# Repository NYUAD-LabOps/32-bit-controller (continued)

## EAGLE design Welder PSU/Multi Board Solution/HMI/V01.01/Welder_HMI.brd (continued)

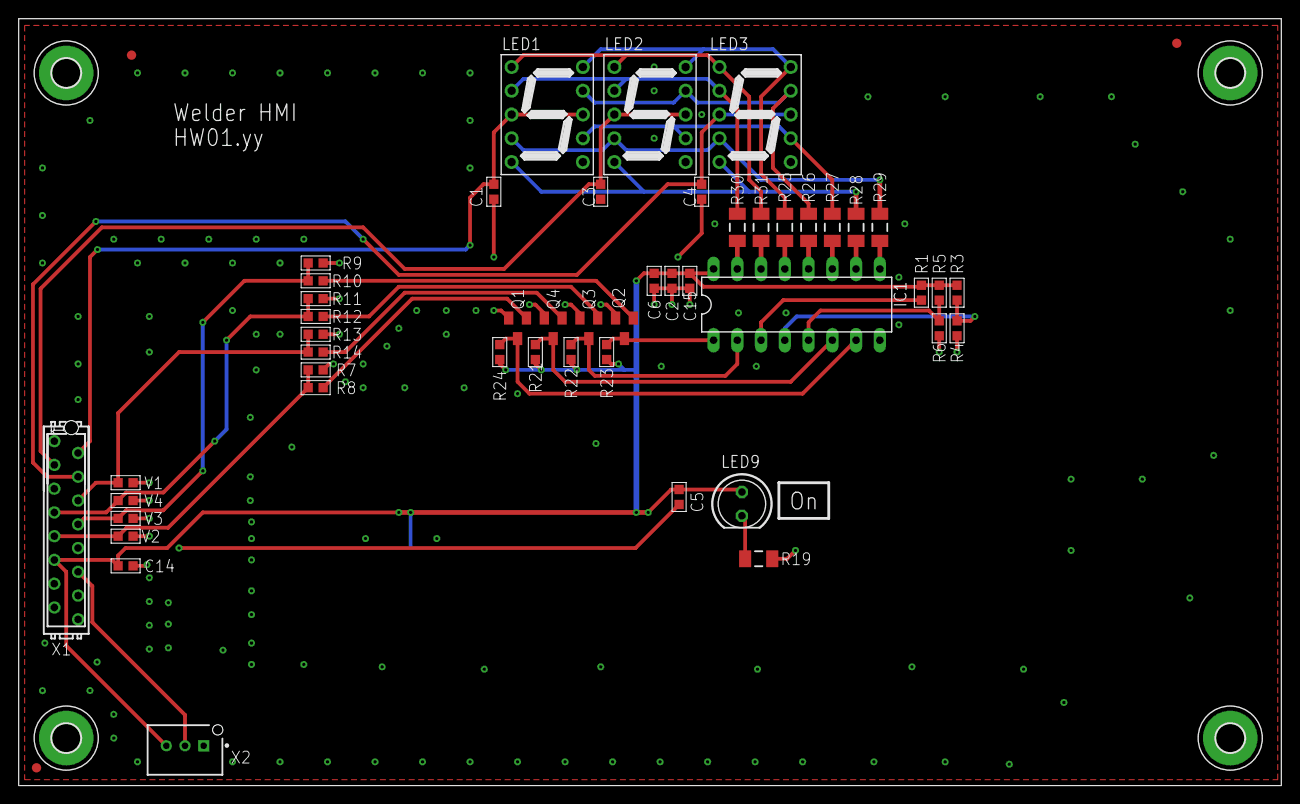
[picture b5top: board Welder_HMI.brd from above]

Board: 2 copper layers, 135.0 x 82.0 mm, 55 parts (0 on the bottom side), 36 nets.

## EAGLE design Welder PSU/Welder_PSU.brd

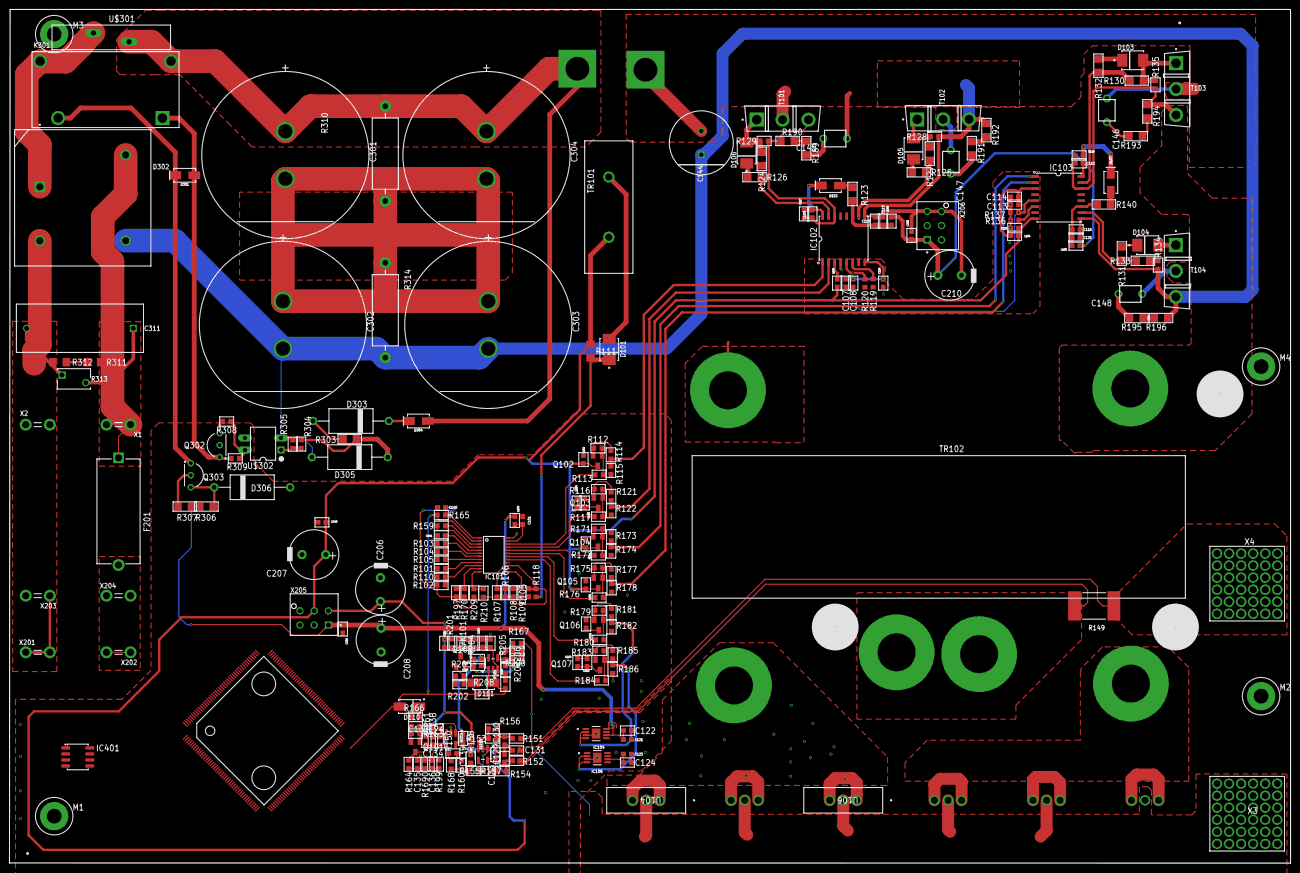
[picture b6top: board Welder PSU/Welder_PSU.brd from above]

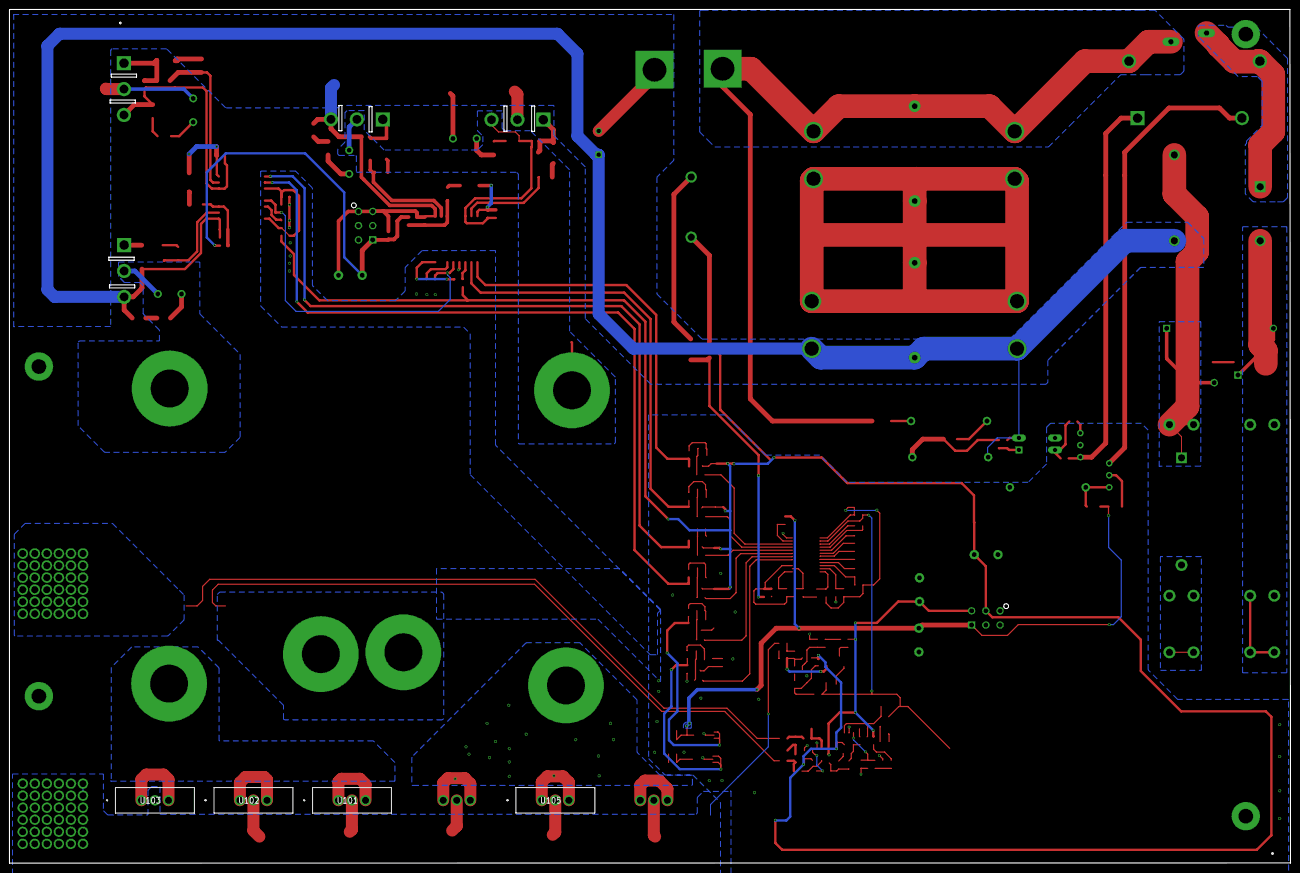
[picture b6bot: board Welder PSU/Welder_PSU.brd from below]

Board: 2 copper layers, 270.1 x 180.0 mm, 246 parts (4 on the bottom side), 126 nets.

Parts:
47K101: R0603
C101, C121, C123, C140: 1µF/25V; 0603
C102, C103, C104, C106, C111, C112: 100nF/50V; 0603
C105: 1nF 50V; C0603
C107, C113, C114, C117, C125, C141: 100nF/100V; 0603
C108, C126: 1uF/35V; 0603
C109, C110, C115, C116, C119, C120: 2.2µF/25V; 0603
C118, C122, C124, C133: 100nF/16V; 0603
C129, C130, C132, C134, C137, C138, C151, C152: 1nF 50V; 0603
C131: 100pF 50V; 0603
C135, C149: 100nF 50V; 0603
C136, C150: 220nF 50V; 0603
C139: 100nF 25V; 0603
C142, C143: 1uF/25V; 0603
C144: 860011378008; RADIAL_D13.0P5.0H25.0
C145, C146, C147, C148: FG26X7R2J472KNT06; CAP_DISC_P5H13
C153: 10nF 25V; 0603
C201, C202, C203, C205: 100nF/ 100V; 0603
C206, C207, C208, C210: 50PX470MEFC10X20; CAPACITOR-ELKO-RM5-10X16
C301, C302, C303, C304: C_1500UFCAP_SLP152M250H9P3_MODIFIED; CAP_SLP152M250H9P3_MODIFIED
C311: R49AN347050B1MKEMET_R49AN347050B1M_0_0; KEMET_R49AN347050B1M_0
D101, D103, D104, D105, D106: STTH1R04U; SMB
D102, D107, D301, D304: RS1M-13-F; SMA-DIODE
D110, D111: SS14; SMA
D302: GBPC3510W1.5MM_DRILL; GBPC3510W_MODIFIED
D303: 1N5387BRLG; DO-201AD
D305, D306: BZX79C9V1; DO-201AD
F201: 696101000002; FUSE_RM22.6
IC101: UCC28951PWR; TSSOP24
IC102, IC103: UCC21542DWK; SOIC16_HV
IC104, IC106: UCC27524DGNVSS; VSSOP-8
IC105, IC108: OPA378AIDBVR; SOT-23-5
IC401: SN65HVD3082EDR; SOIC8
K301: PANASONIC_ALFG2PF09_MODIFIED; PANASONIC_ALFG2PF09_0_MODIFIED
L102, L103, L104, L105, L108: BLM18RK601SN1D; 0603
M1, M2, M3, M4: M_HOLE_3M; PCB_SCREW_M3_POWER
PAD101, PAD102: THT_PAD_5MM; THT_PAD_D5.0
Q101, Q102, Q103, Q104, Q105, Q106, Q107, Q108: 2N7002; SOT23
Q302: KSD1616AYTA; TO-92
Q303: BC640TA; TO-92
R101, R102, R105, R199: 100K 1%; R0603
R103, R104, R107, R109, R115, R122, R158, R162, R163, R174, R178, R182, R186, R202, R203: 10K 1%; R0603
R106, R108, R159, R166, R208, R210: 0R 1%; R0603
R110: 49K9 1%; R0603
R111: 10R 1%; R1206
R112, R116, R171, R175, R179, R183: 100R 1%; R0603
R113, R117, R172, R176, R180, R184: 10R 1%; R0603
R114, R121, R173, R177, R181, R185: 330R; R0603
R118: 22R 1%; R0603
R119, R120, R136, R137: 10K; R0603
R123, R124, R125, R126, R127, R130, R131, R132, R133, R140: 2R2 1%; R1206
R128, R129, R134, R135: 49K9; R0603
R149: WSL5931L3000FEA; WSLP3921
R150, R207: 100k 1%; R0603
R151, R152: 590R 1%; R0603
R153, R154: 412R 1%; R0603
R155, R156, R1690: 47K 1%; R0603
R157, R167: 1K2 1%; R0603
R160, R200, R308, R309: R0603
R161, R201: 1k; R0603
R164, R204, R205: 100K; R0603
R165: 18K 1%; R0603
R168, R206: 18k 1%; R0603
R170, R197, R209: 10k 1%; R0603
R189, R190, R191, R192, R193, R194, R195, R196: 10K; R1206
R303: 82K, 1%; R1206
R304: 36K,5%; R0603
R305: 100K,5%; R0603
R306: 100R 1%; R1206
R307: 1K 1%; R1206
R310, R314: 51K 5%; RES-RM20-RSF3W
R311, R312: 220K 5% CRCW1206220KJNEAHP; R1206
R313: B72205S0271K1011; EPCOS_B72205S0271K101_MODIFIED
T101, T102, T103, T104: SIHG039N60EF"; TO-247AC_MODIFIED
TR101: CST206-2A1.5MM-DRILL; CST206-2A_MODIFIED
TR102: TRANSFORMER-CUSTOM-PSFB; TOROID_B64290A0705X830
U101, U102, U103, U104, U105, U106: FEP30DP-E3/45; TO-247AD_VIS
U401: S7G2LQFP176; LQFP176_24X24
U$101: OPA378AIDBVR; SOT-23-5
U$301: B57364S100M54; VARISTOR_D25_P7.5
U$302: PC817; DIP04
X1, X2, X201, X202, X203, X204: 726386-2; TE_726386-2_MODIFIED
X3: 7461061; X01_M10_7461061
X4: 7461061"; X01_M10_7461061_MODIFIED
X205, X206: MOLEX_206832-0601MOLEX_206832-0601; MOLEX_206832-0601

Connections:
10_PSFB_CONVERTER:AN_OUTA: IC102.15, R124.2, R126.2
10_PSFB_CONVERTER:AN_OUTB: IC102.10, R125.2, R127.2
10_PSFB_CONVERTER:AN_OUTC: IC103.15, R130.2, R132.2
10_PSFB_CONVERTER:AN_OUTD: IC103.10, R131.2, R133.2
10_PSFB_CONVERTER:CTRLR_OUTA: IC101.22, R113.1
10_PSFB_CONVERTER:CTRLR_OUTB: IC101.21, R117.1
10_PSFB_CONVERTER:CTRLR_OUTC: IC101.20, R172.1
10_PSFB_CONVERTER:CTRLR_OUTD: IC101.19, R176.1
10_PSFB_CONVERTER:CTRLR_OUTE: IC101.18, R180.1
10_PSFB_CONVERTER:CTRLR_OUTF: IC101.17, R184.1
10_PSFB_CONVERTER:EA_IN: D110.2, D111.2, IC101.2, R165.2, R166.1, R208.1
10_PSFB_CONVERTER:GATE_DRV_DIS: IC102.5, IC103.5, R120.1, R137.1
10_PSFB_CONVERTER:G_DRV_INA: IC102.1, R114.1, R115.1
10_PSFB_CONVERTER:G_DRV_INB: IC102.2, R121.1, R122.1
10_PSFB_CONVERTER:G_DRV_INC: IC103.1, R173.1, R174.1
10_PSFB_CONVERTER:G_DRV_IND: IC103.2, R177.1, R178.1
10_PSFB_CONVERTER:G_DRV_INE: IC104.2, IC104.4, R181.1, R182.1
10_PSFB_CONVERTER:G_DRV_INF: IC106.2, IC106.4, R185.1, R186.1
10_PSFB_CONVERTER:N$1: IC101.12, R209.2, R210.1
10_PSFB_CONVERTER:N$2: IC101.6, R103.2
10_PSFB_CONVERTER:N$3: IC101.7, R104.2
10_PSFB_CONVERTER:N$4: IC101.8, R105.2
10_PSFB_CONVERTER:N$5: IC102.6, R119.1
10_PSFB_CONVERTER:N$6: IC101.14, R106.2, R107.2
10_PSFB_CONVERTER:N$7: IC101.9, R101.1
10_PSFB_CONVERTER:N$8: IC101.13, R108.2, R109.2
10_PSFB_CONVERTER:N$9: IC101.10, R102.2, R110.2
10_PSFB_CONVERTER:N$10: D106.1, R126.1
10_PSFB_CONVERTER:N$11: D101.2, TR101.1
10_PSFB_CONVERTER:N$12: D101.1, R111.1, R118.2
10_PSFB_CONVERTER:N$13: Q102.1, R112.1, R113.2
10_PSFB_CONVERTER:N$14: Q102.2, R112.2, R114.2
10_PSFB_CONVERTER:N$15: C116.1, C120.1, IC103.11, L105.2, R140.1
10_PSFB_CONVERTER:N$16: D105.1, R125.1
10_PSFB_CONVERTER:N$17: Q103.1, R116.1, R117.2
10_PSFB_CONVERTER:N$18: Q103.2, R116.2, R121.2
10_PSFB_CONVERTER:N$19: C107.2, C108.2, C125.2, IC102.3, IC102.8, L102.2
10_PSFB_CONVERTER:N$20: C109.1, C117.2, D102.C, IC102.16
10_PSFB_CONVERTER:N$21: D105.2, R127.1, R128.2, T102.1
10_PSFB_CONVERTER:N$22: D102.A, R123.2
10_PSFB_CONVERTER:N$23: C110.1, C119.1, IC102.11, L103.1, R123.1
10_PSFB_CONVERTER:N$24: D106.2, R124.1, R129.2, T101.1
10_PSFB_CONVERTER:N$26: TR102.3, U101.1, U101.3, U102.1, U102.3, U103.1, U103.3
10_PSFB_CONVERTER:N$27: IC103.6, R136.1
10_PSFB_CONVERTER:N$28: C113.2, C114.2, C126.2, IC103.3, IC103.8, L104.1
10_PSFB_CONVERTER:N$29: TR102.6, U104.1, U104.3, U105.1, U105.3, U106.1, U106.3
10_PSFB_CONVERTER:N$30: D103.1, R132.1
10_PSFB_CONVERTER:N$31: C115.1, C118.2, D107.C, IC103.16
10_PSFB_CONVERTER:N$32: C101.1, IC101.23, L108.1
10_PSFB_CONVERTER:N$33: D104.1, R131.1
10_PSFB_CONVERTER:N$34: D104.2, R133.1, R134.2, T104.1
10_PSFB_CONVERTER:N$35: C145.2, R189.2
10_PSFB_CONVERTER:N$36: D107.A, R140.2
10_PSFB_CONVERTER:N$38: D103.2, R130.1, R135.2, T103.1
10_PSFB_CONVERTER:N$39: Q104.1, R171.1, R172.2
10_PSFB_CONVERTER:N$40: Q104.2, R171.2, R173.2
10_PSFB_CONVERTER:N$45: IC101.11, R170.2, R197.2
10_PSFB_CONVERTER:N$47: C129.1, R152.1, R154.1
10_PSFB_CONVERTER:N$48: C129.2, C130.1, C131.2
10_PSFB_CONVERTER:N$49: C130.2, R151.1, R153.1
10_PSFB_CONVERTER:N$50: R153.2, R156.2, U$101.3
10_PSFB_CONVERTER:N$51: R154.2, R155.2, U$101.4
10_PSFB_CONVERTER:N$52: R155.1, R157.2, U$101.1
10_PSFB_CONVERTER:N$53: R189.1, R190.2
10_PSFB_CONVERTER:N$54: C134.1, R160.1
10_PSFB_CONVERTER:N$55: IC101.4, R159.2
10_PSFB_CONVERTER:N$56: Q101.3, R161.1, R164.2
10_PSFB_CONVERTER:N$57: C135.1, R164.1, R1690.2
10_PSFB_CONVERTER:N$58: C136.1, IC108.3, R199.2, R1690.1
10_PSFB_CONVERTER:N$59: C137.2, R150.2
10_PSFB_CONVERTER:N$61: Q101.1, R162.1, R163.2
10_PSFB_CONVERTER:N$62: Q105.1, R175.1, R176.2
10_PSFB_CONVERTER:N$63: C137.1, C138.1, D110.1, IC108.1, R166.2
10_PSFB_CONVERTER:N$64: IC101.3, R159.1
10_PSFB_CONVERTER:N$65: Q105.2, R175.2, R177.2
10_PSFB_CONVERTER:N$66: C147.2, R191.2
10_PSFB_CONVERTER:N$67: Q106.1, R179.1, R180.2
10_PSFB_CONVERTER:N$68: Q106.2, R179.2, R181.2
10_PSFB_CONVERTER:N$69: R191.1, R192.2
10_PSFB_CONVERTER:N$70: Q107.1, R183.1, R184.2
10_PSFB_CONVERTER:N$71: Q107.2, R183.2, R185.2
10_PSFB_CONVERTER:N$72: R195.1, R196.2
10_PSFB_CONVERTER:N$73: C148.2, R195.2
10_PSFB_CONVERTER:N$74: R193.1, R194.2
10_PSFB_CONVERTER:N$75: C146.2, R193.2
10_PSFB_CONVERTER:N$76: Q108.3, R201.1, R204.2
10_PSFB_CONVERTER:N$77: C134.2, C138.2, IC108.4, R150.1, R168.2
10_PSFB_CONVERTER:N$78: 47K101.2, C149.1, R204.1
10_PSFB_CONVERTER:N$79: 47K101.1, C150.1, IC105.3, R205.2
10_PSFB_CONVERTER:N$80: Q108.1, R202.1, R203.2
10_PSFB_CONVERTER:N$81: C151.2, R207.2
10_PSFB_CONVERTER:N$82: C151.1, C152.1, D111.1, IC105.1, R208.2
10_PSFB_CONVERTER:N$83: C132.1, R200.1
10_PSFB_CONVERTER:N$84: C132.2, C152.2, IC105.4, R206.2, R207.1
10_PSFB_CONVERTER:VREF: C140.1, IC101.1, R102.1, R165.1, R197.1, R209.1
10_PSFB_CONVERTER:VSS_A: C109.2, C117.1, C147.1, IC102.14, R129.1, R190.1, T101.3, T102.2, TR102.2
10_PSFB_CONVERTER:VSS_C: C115.2, C118.1, C148.1, IC103.14, R135.1, R194.1, T103.3, T104.2, TR102.1
10_PSFB_CONVERTER:V_CS_F: C105.1, IC101.15, R106.1, R108.1, R118.1
10_PSFB_CONVERTER:V_FEEDBACK: R167.1, R200.2, R206.1
10_PSFB_CONVERTER:V_I_FEEDBACK: R157.1, R158.2, R160.2, R168.1
20_POWER_SUPPLY:N$1: F201.2, X202.1, X202.1-2, X204.1, X204.1-2
30_MAINS_INPUT_PFC1:GND_LV: D301.A, K301.1, Q303.1, R309.1
30_MAINS_INPUT_PFC1:N$1: C301.2, C302.1, C303.1, C304.2, R310.1, R314.2
30_MAINS_INPUT_PFC1:N$2: D302.1, K301.4, U$301.1
30_MAINS_INPUT_PFC1:N$3: D301.C, K301.2, Q302.1
30_MAINS_INPUT_PFC1:N$5: Q302.2, R306.2
30_MAINS_INPUT_PFC1:N$6: D303.K, D304.C
30_MAINS_INPUT_PFC1:N$7: D303.A, R303.2
30_MAINS_INPUT_PFC1:N$8: R304.2, R305.1, U$302.1
30_MAINS_INPUT_PFC1:N$9: D305.K, R303.1, R304.1
30_MAINS_INPUT_PFC1:N$12: D306.K, Q302.3, R307.2
30_MAINS_INPUT_PFC1:N$13: R311.1, R312.2
30_MAINS_INPUT_PFC1:N$16: Q303.3, R308.1
30_MAINS_INPUT_PFC1:N$17: R308.2, R309.2, U$302.4
GND: C101.2, C102.1, C103.1, C104.1, C105.2, C106.1, C107.1, C108.1, C111.1, C112.1, C113.1, C114.1, C121.2, C122.1, C123.2, C124.1, C125.1, C126.1, C131.1, C133.2, C135.2, C136.2, C139.2, C140.2, C141.2, C142.2, C143.2, C149.2, C150.2, C153.2, C201.2, C202.2, C205.2, C206.2, C207.2, C208.2, D306.A, IC101.24, IC102.4, IC103.4, IC104.3, IC104.3-2, IC105.2, IC106.3, IC106.3-2, IC108.2, M1.1, Q101.2, Q108.2, Q303.2, R101.2, R103.1, R104.1, R105.1, R107.1, R109.1, R110.1, R111.2, R115.2, R119.2, R120.2, R122.2, R136.2, R137.2, R149.1, R152.2, R156.1, R163.1, R170.1, R174.2, R178.2, R182.2, R186.2, R199.1, R203.1, R205.1, R210.2, TR101.2, TR102.4, TR102.5, U$101.2, U$302.3, X205.5, X205.6
GND2: C110.2, C116.2, C119.2, C120.2, C144.1, C203.2, C210.2, C302.2, C303.2, D302.3, D305.A, IC102.9, IC103.9, R128.1, R134.1, R192.1, R196.1, R305.2, R314.1, T102.3, T104.3, U$302.2, X206.5, X206.6
MAINS_L: C311.1, D302.4, F201.1, R311.2, R313.2, X1.1, X1.1-2
MAINS_N: C311.2, D302.2, R312.1, R313.1, X2.1, X2.1-2, X201.1, X201.1-2, X203.1, X203.1-2
unnamed: C141.1, IC101.5
unnamed: R167.2, U101.2, U102.2, U103.2, U104.2, U105.2, U106.2, X3.1, X3.1-1, X3.1-2, X3.1-3, X3.1-4, X3.1-5, X3.1-6, X3.1-7, X3.1-8, X3.1-9, X3.1-10, X3.1-11, X3.1-12, X3.1-13, X3.1-14, X3.1-15, X3.1-16, X3.1-17, X3.1-18, X3.1-19, X3.1-20, X3.1-21, X3.1-22, X3.1-23, X3.1-24, X3.1-25, X3.1-26, X3.1-27, X3.1-28, X3.1-29, X3.1-30, X3.1-31, X3.1-32, X3.1-33, X3.1-34, X3.1-35
V_3V3: C102.2, C103.2, C104.2, C106.2, C133.1, C139.1, C143.1, C153.1, C201.1, C207.1, IC105.5, IC108.5, L102.1, L104.2, Q102.3, Q103.3, Q104.3, Q105.3, U$101.5, X205.4
V_5V0: C202.1, C206.1, R158.1, R161.2, R201.2, X205.2
V_12V0: C111.2, C112.2, C121.1, C122.2, C123.1, C124.2, C142.1, C205.1, C208.1, IC104.6, IC106.6, L108.2, Q106.3, Q107.3, R306.1, R307.1, X205.1
V_12V0_AUX: C203.1, C210.1, L103.2, L105.1, X206.1
V_RECT_F_PLUS: C144.2, C145.1, C146.1, C301.1, C304.1, D304.A, K301.3, PAD101.P$1, PAD102.P$1, R310.2, T101.2, T103.2, U$301.2
WELD-: R149.2, R151.2, X4.1, X4.1-1, X4.1-2, X4.1-3, X4.1-4, X4.1-5, X4.1-6, X4.1-7, X4.1-8, X4.1-9, X4.1-10, X4.1-11, X4.1-12, X4.1-13, X4.1-14, X4.1-15, X4.1-16, X4.1-17, X4.1-18, X4.1-19, X4.1-20, X4.1-21, X4.1-22, X4.1-23, X4.1-24, X4.1-25, X4.1-26, X4.1-27, X4.1-28, X4.1-29, X4.1-30, X4.1-31, X4.1-32, X4.1-33, X4.1-34, X4.1-35

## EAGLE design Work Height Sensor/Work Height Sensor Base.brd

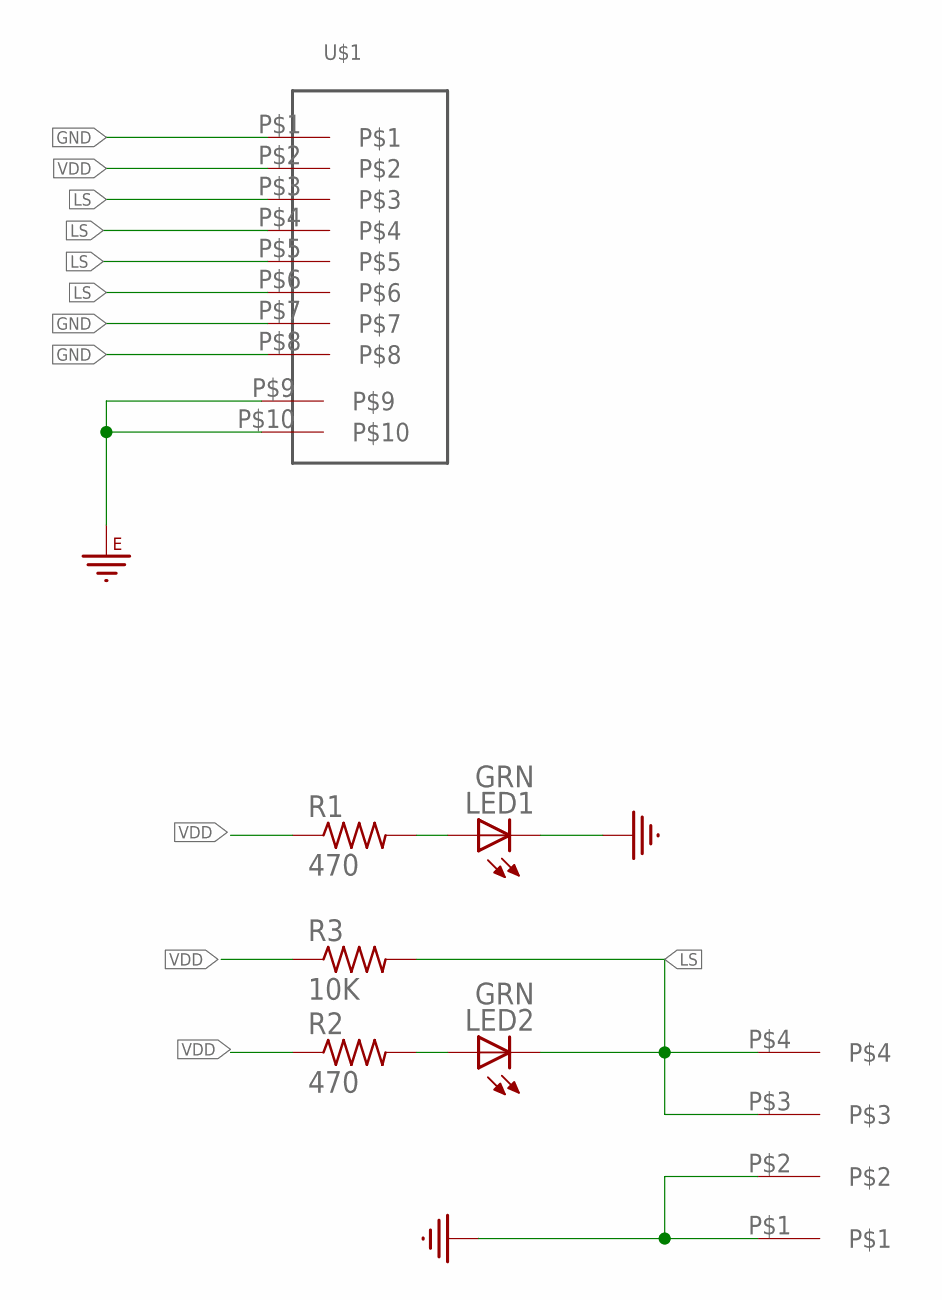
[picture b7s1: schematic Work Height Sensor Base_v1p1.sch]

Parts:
J1: 3.81MM_1_X_4_RT_ANGLE_PLUG_HEADER; 1X4_3.81MM_PITCH
LED1, LED2: LED_0805_GREEN
R1, R2: 470; 0402
R3: 10K; 0402
U$1: RJ45_SMTRJ; RJ45_SMT

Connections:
GND: J1.P$1, J1.P$2, LED1.C, U$1.P$1, U$1.P$7, U$1.P$8
GNDE: U$1.P$9, U$1.P$10
LS: J1.P$3, J1.P$4, LED2.C, R3.P$2 (2), U$1.P$3, U$1.P$4, U$1.P$5, U$1.P$6
unnamed: LED2.A, R2.P$2 (2)
unnamed: LED1.A, R1.P$2 (2)
VDD: R1.P$1 (1), R2.P$1 (1), R3.P$1 (1), U$1.P$2

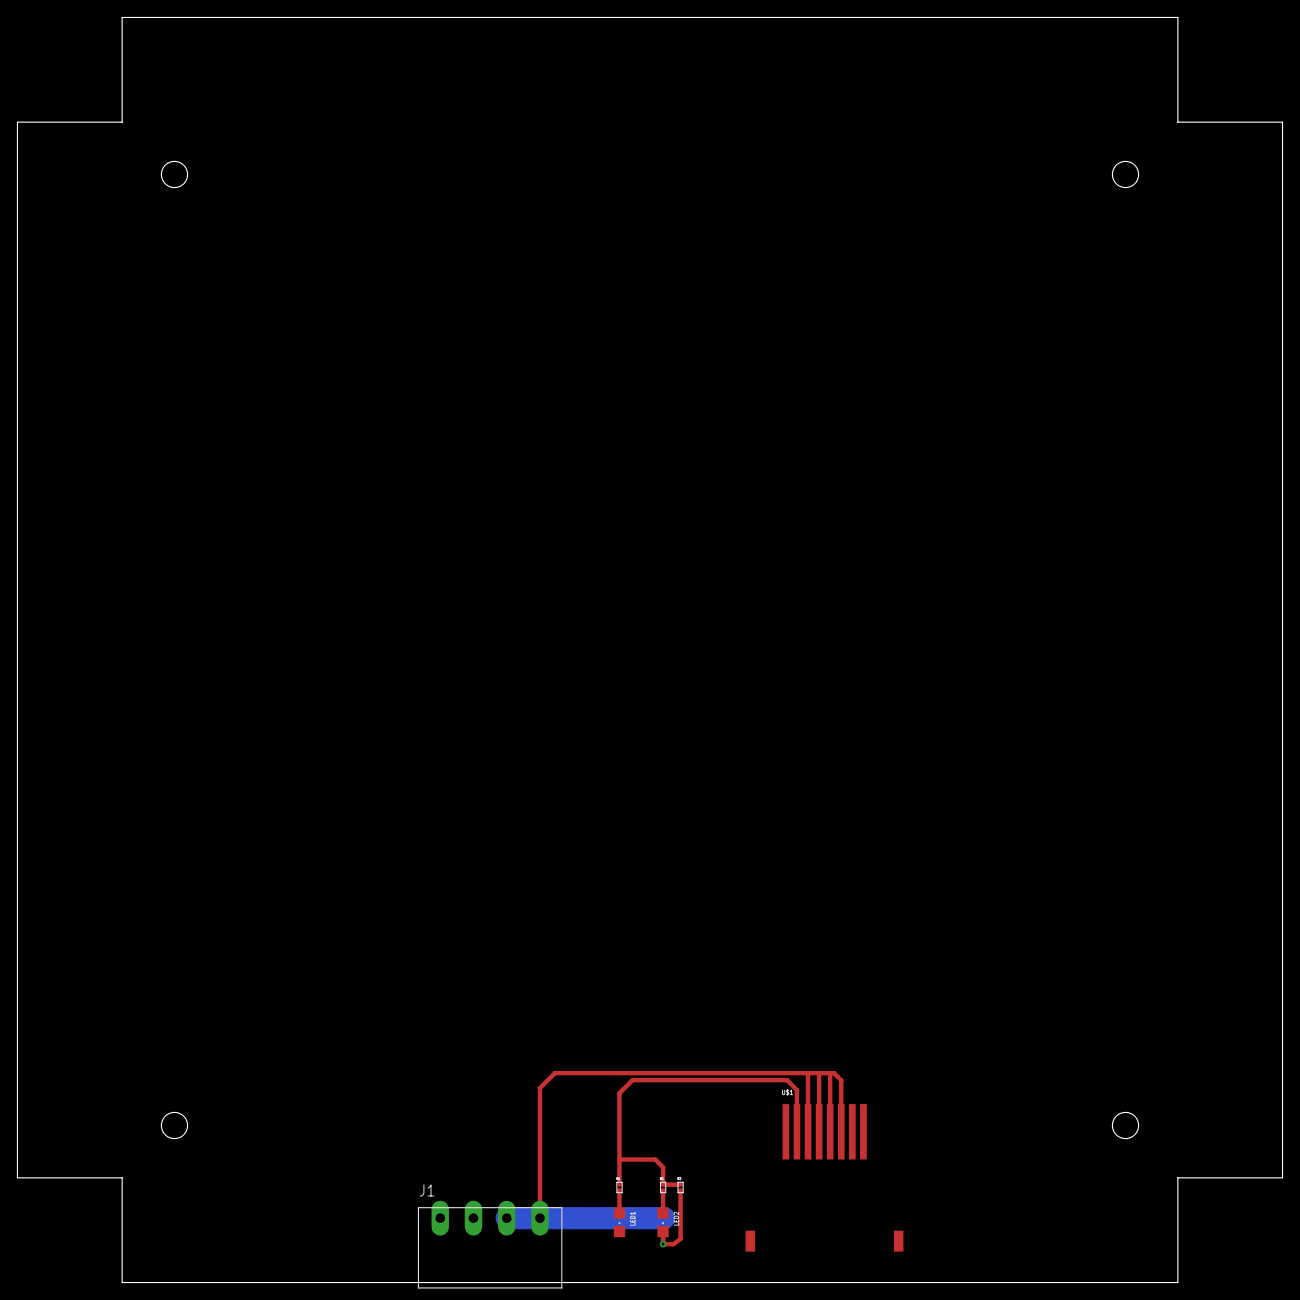
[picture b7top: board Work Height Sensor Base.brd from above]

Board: 2 copper layers, 145.0 x 145.0 mm, 7 parts (0 on the bottom side), 6 nets.
